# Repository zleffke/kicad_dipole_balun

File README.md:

# kicad_dipole_balun
KiCAD design for passive dipole balun based on minicircuits components.
It is anticipated that primarily standard tape measure elements will be used as the actual antenna elements, though this is not a strict requirement.

### Minicircuits Transformer: [ADT1.5-122+](https://www.minicircuits.com/WebStore/dashboard.html?model=ADT1.5-122%2B)
These designs are priarily based on this tranformer which is a 1:1.5 ratio SMT transformer designed to match 50 ohms unbalanced coax to a ~75 ohm balanced impedance (i.e. dipole feedpoint).  This model is useable from 20-1200 MHz per datasheet, so may be useful for VHF, UHF, and lower microwave (ADSB & 23cm) designs.

### Version 1, rev-, 20201123
This variant is designed to accept 1/4" tape measure elements using #2 screws.  Rev- submitted to osh park 20201123.  First intended project (test frequency) is ADSB reception at 1090 MHz.

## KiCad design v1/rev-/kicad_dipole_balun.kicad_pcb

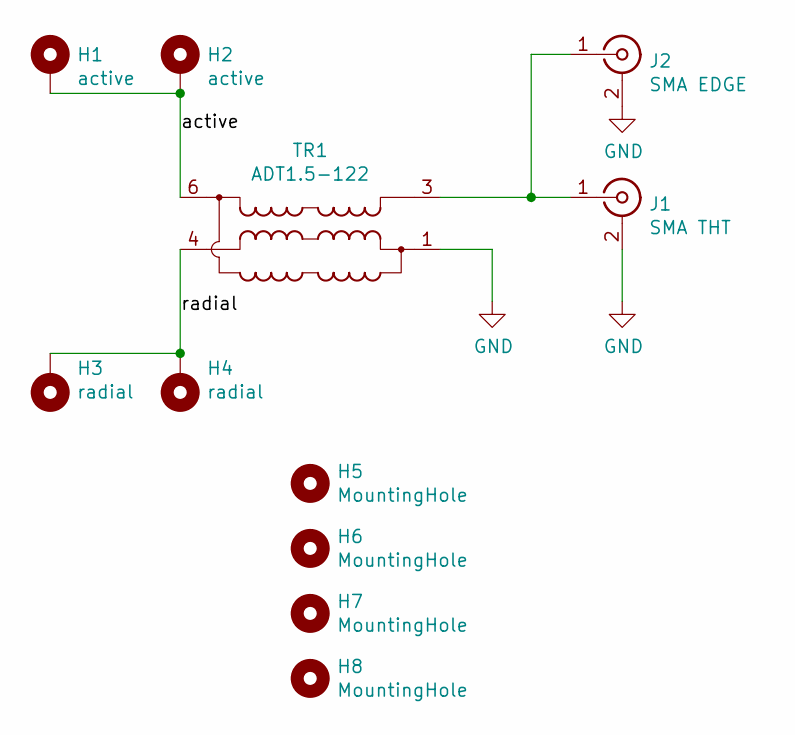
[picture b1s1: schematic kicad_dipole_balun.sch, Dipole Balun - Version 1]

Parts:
H1, H2: active; MountingHole_2.5mm_Pad_Via
H3, H4: radial; MountingHole_2.5mm_Pad_Via
H5, H6, H7, H8: MountingHole; MountingHole_3.2mm_M3
J1: SMA THT; SMA_Amphenol_132134_Vertical
J2: SMA EDGE; SMA_Samtec_SMA-J-P-X-ST-EM1_EdgeMount
TR1: ADT1.5-122; Mini-Circuits_CD542_H2.84mm

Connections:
/active: H1.1, H2.1, TR1.6
/radial: H3.1, H4.1, TR1.4
GND: J1.2 (Ext), J2.2 (Ext), TR1.1, TR1.2
unnamed: J1.1 (In), J2.1 (In), TR1.3

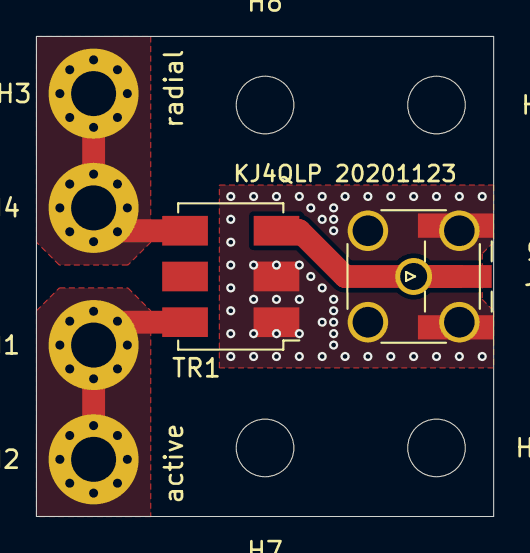
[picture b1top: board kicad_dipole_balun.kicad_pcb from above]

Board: 2 copper layers, 25.4 x 26.7 mm, 11 parts (0 on the bottom side), 4 nets.

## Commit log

2020-11-24 first variant, this commit submitted to osh park.

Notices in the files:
v1/rev-/kicad_dipole_balun.sch:
creativecommons.org/licenses/by/4.0
License: CC BY 4.0
